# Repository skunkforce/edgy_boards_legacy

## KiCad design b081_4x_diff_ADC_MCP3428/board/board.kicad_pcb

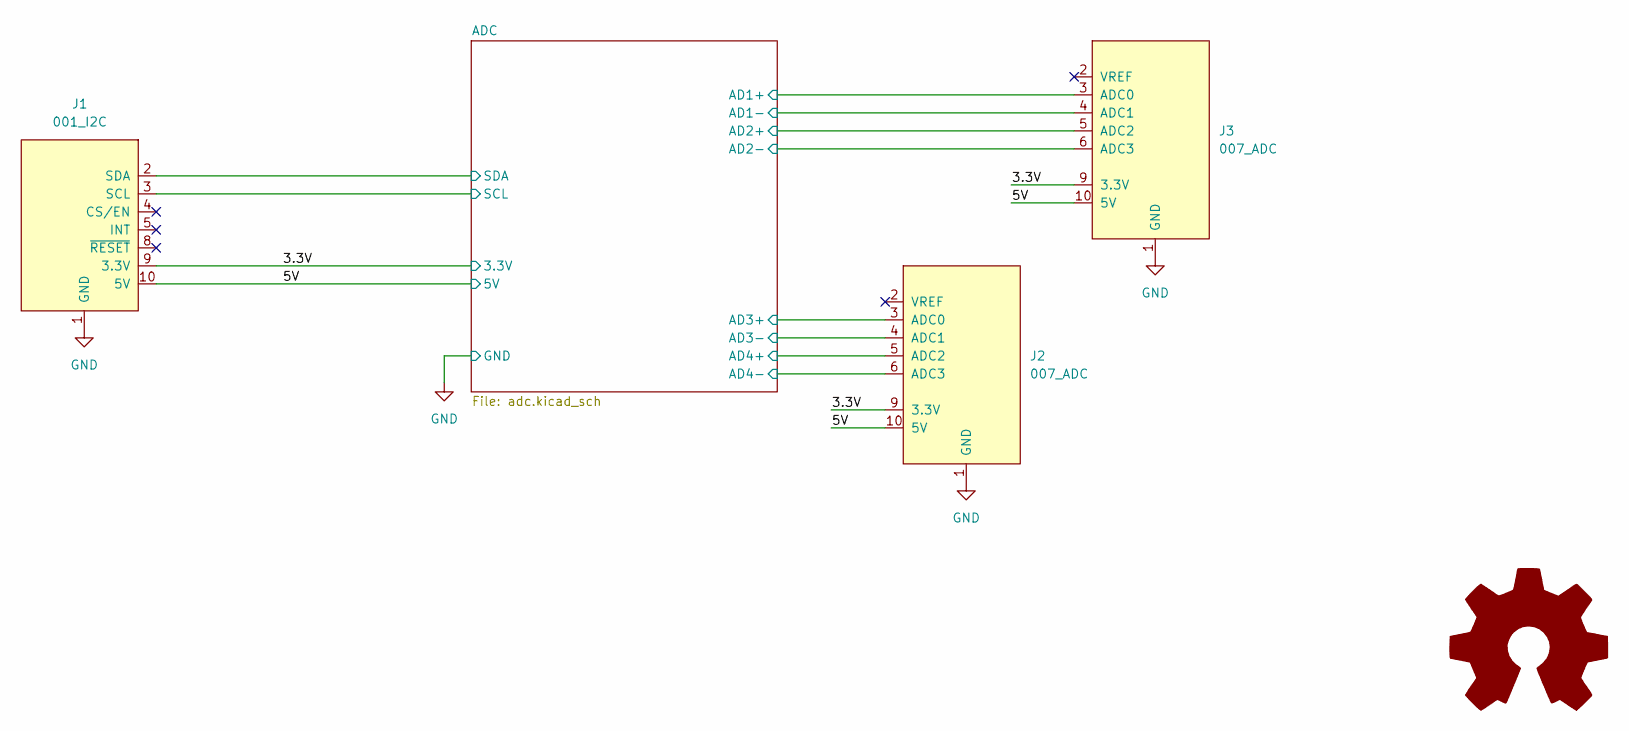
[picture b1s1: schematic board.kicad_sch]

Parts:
J1: 001_I2C; on_edge_2x05_device
J2, J3: 007_ADC; on_edge_2x05_host
l1: Logo_Open_Hardware_Larg; OSHW-Logo2_7.3x6mm_SilkScreen

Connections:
/3.3V: J1.9 (3.3V), J2.9 (3.3V), J3.9 (3.3V); also elsewhere on the board
/5V: J1.10 (5V), J2.10 (5V), J3.10 (5V); also elsewhere on the board
/ADC/AD1+: J3.3 (ADC0); also elsewhere on the board
/ADC/AD1-: J3.4 (ADC1); also elsewhere on the board
/ADC/AD2+: J3.5 (ADC2); also elsewhere on the board
/ADC/AD2-: J3.6 (ADC3); also elsewhere on the board
/ADC/AD3+: J2.3 (ADC0); also elsewhere on the board
/ADC/AD3-: J2.4 (ADC1); also elsewhere on the board
/ADC/AD4+: J2.5 (ADC2); also elsewhere on the board
/ADC/AD4-: J2.6 (ADC3); also elsewhere on the board
/ADC/SCL: J1.3 (SCL); also elsewhere on the board
/ADC/SDA: J1.2 (SDA); also elsewhere on the board
GND: J1.1 (GND), J2.1 (GND), J3.1 (GND); also elsewhere on the board

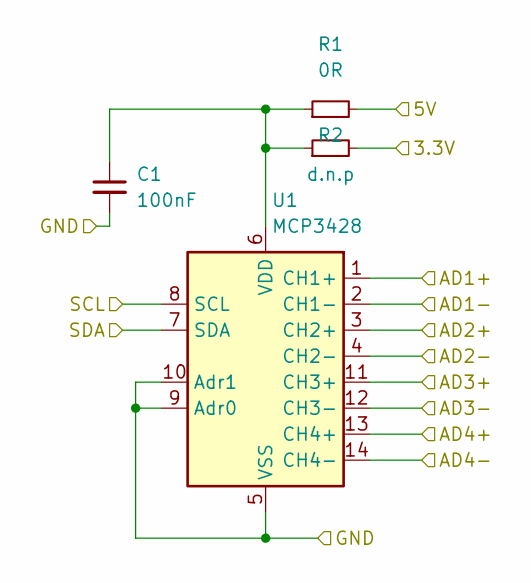
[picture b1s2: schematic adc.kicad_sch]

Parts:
C1: 100nF; C_0603_1608Metric
R1: 0R; R_0603_1608Metric
R2: d.n.p; R_0603_1608Metric
U1: MCP3428; SOIC-14_3.9x8.7mm_P1.27mm

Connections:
/3.3V: R2.2; also elsewhere on the board
/5V: R1.2; also elsewhere on the board
/ADC/AD1+: U1.1 (CH1+); also elsewhere on the board
/ADC/AD1-: U1.2 (CH1-); also elsewhere on the board
/ADC/AD2+: U1.3 (CH2+); also elsewhere on the board
/ADC/AD2-: U1.4 (CH2-); also elsewhere on the board
/ADC/AD3+: U1.11 (CH3+); also elsewhere on the board
/ADC/AD3-: U1.12 (CH3-); also elsewhere on the board
/ADC/AD4+: U1.13 (CH4+); also elsewhere on the board
/ADC/AD4-: U1.14 (CH4-); also elsewhere on the board
/ADC/SCL: U1.8 (SCL); also elsewhere on the board
/ADC/SDA: U1.7 (SDA); also elsewhere on the board
GND: C1.2, U1.5 (VSS), U1.9 (Adr0), U1.10 (Adr1); also elsewhere on the board
unnamed: C1.1, R1.1, R2.1, U1.6 (VDD)

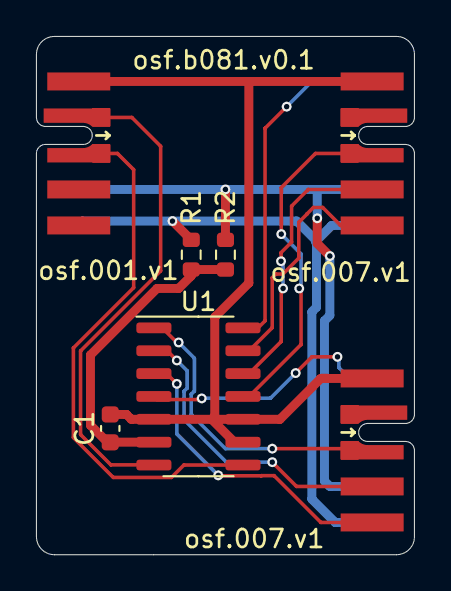
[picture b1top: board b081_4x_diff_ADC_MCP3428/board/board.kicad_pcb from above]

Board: 4 copper layers, 21.0 x 28.8 mm, 8 parts (1 on the bottom side), 14 nets.

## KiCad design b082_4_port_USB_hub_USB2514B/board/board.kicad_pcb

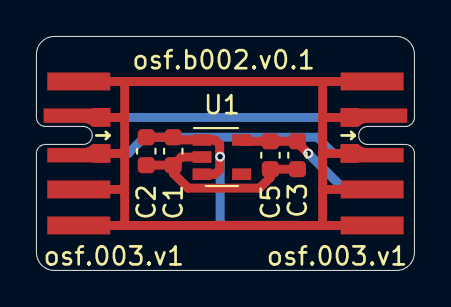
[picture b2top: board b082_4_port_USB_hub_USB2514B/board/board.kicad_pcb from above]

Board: 4 copper layers, 21.0 x 13.0 mm, 8 parts (1 on the bottom side), 7 nets.

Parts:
C1: 100nF; C_0603_1608Metric
C2, C5: 1uF; C_0603_1608Metric
C3: 10uF; C_0603_1608Metric
J1: 003_power; on_edge_2x05_device
J2: 003_power; on_edge_2x05_host
U1: TC1017-xCT; SOT-23-5
l1: Logo_Open_Hardware_Larg; OSHW-Logo2_7.3x6mm_SilkScreen

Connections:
GND: C1.2, C2.2, C3.2, C5.2, U1.2 (GND)
unnamed: C1.1, C2.1, J1.10 (5V), J2.10 (5V), U1.1 (VIN), U1.3 (~SHDN)
unnamed: C3.1, C5.1, J2.9 (3.3V), U1.5 (VOUT)
unnamed: J1.1 (GND), J1.2 (GND), J1.3 (GND), J1.4 (GND), J1.5 (GND), J2.1 (GND), J2.2 (GND), J2.3 (GND), J2.4 (GND), J2.5 (GND)
unnamed: J1.6 (1.2V), J2.6 (1.2V)
unnamed: J1.7 (1.8V), J2.7 (1.8V)
unnamed: J1.8 (2.5V), J2.8 (2.5V)

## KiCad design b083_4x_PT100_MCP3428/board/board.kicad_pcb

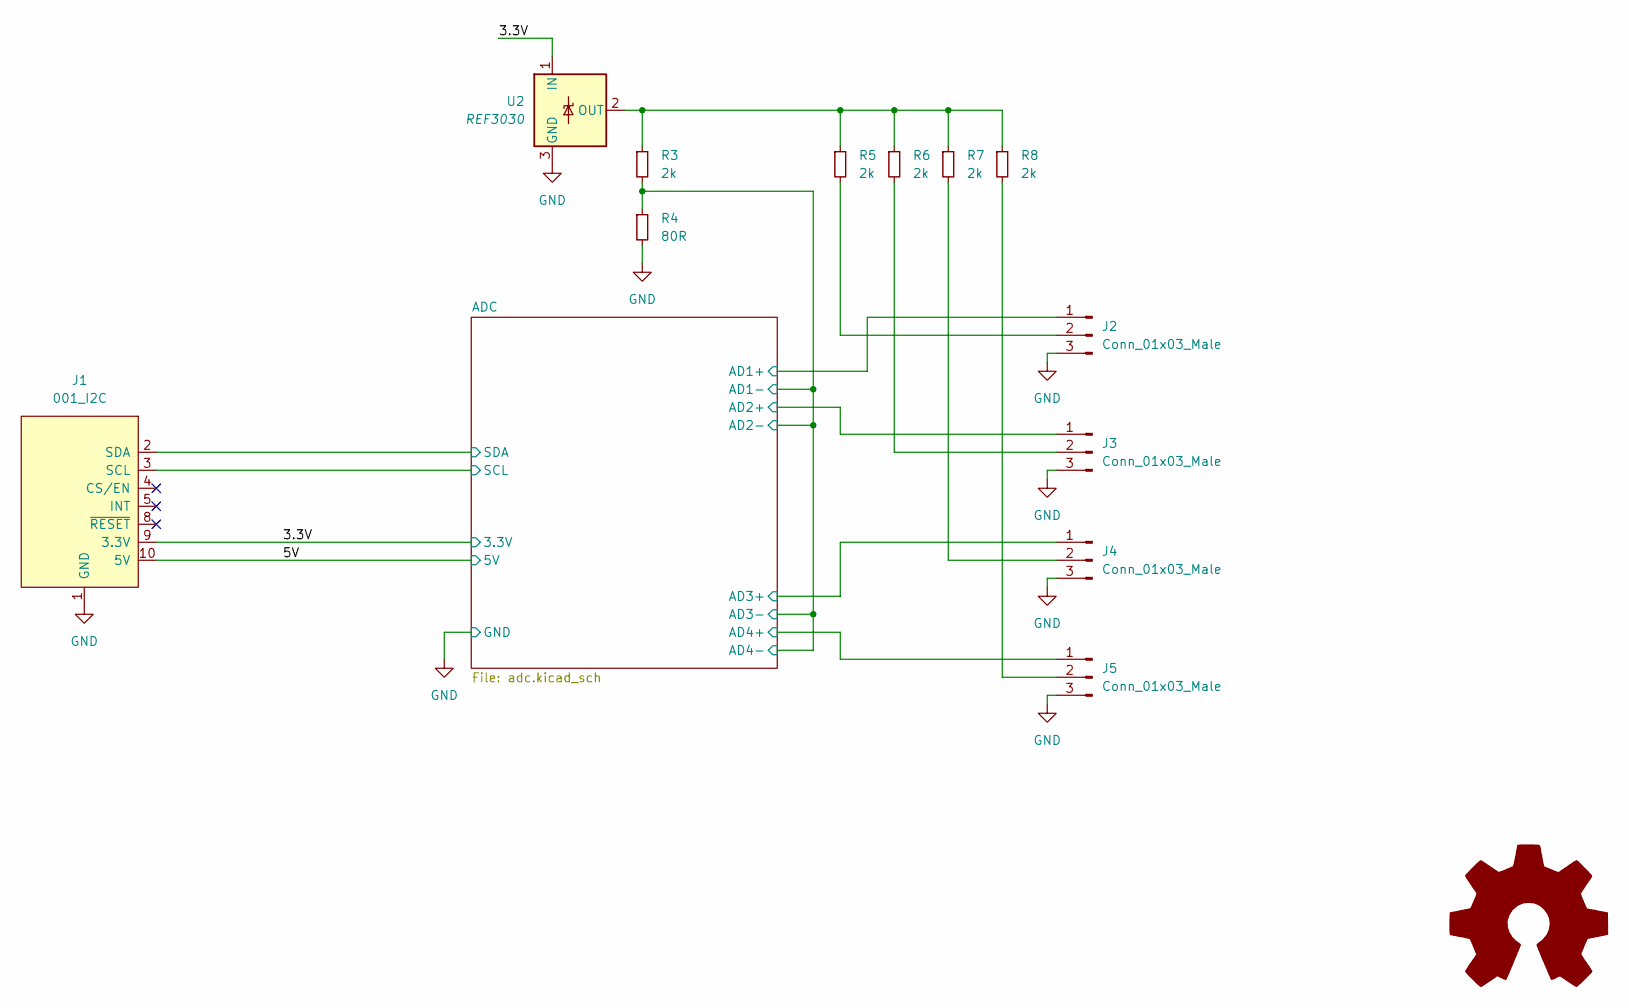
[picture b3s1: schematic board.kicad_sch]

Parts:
J1: 001_I2C; on_edge_2x05_device
J2, J3, J4, J5: Conn_01x03_Male; PinHeader_1x03_P2.54mm_Vertical
R3, R5, R6, R7, R8: 2k; R_0603_1608Metric
R4: 80R; R_0603_1608Metric
U2: REF3030; SOT-23
l1: Logo_Open_Hardware_Larg; OSHW-Logo2_7.3x6mm_SilkScreen

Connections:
/3.3V: J1.9 (3.3V), U2.1 (IN); also elsewhere on the board
/5V: J1.10 (5V)
/ADC/AD1+: J2.1; also elsewhere on the board
/ADC/AD1-: R3.2, R4.1; also elsewhere on the board
/ADC/AD2+: J3.1; also elsewhere on the board
/ADC/AD3+: J4.1; also elsewhere on the board
/ADC/AD4+: J5.1; also elsewhere on the board
/ADC/SCL: J1.3 (SCL); also elsewhere on the board
/ADC/SDA: J1.2 (SDA); also elsewhere on the board
GND: J1.1 (GND), J2.3, J3.3, J4.3, J5.3, R4.2, U2.3 (GND); also elsewhere on the board
unnamed: J2.2, R5.2
unnamed: J3.2, R6.2
unnamed: J4.2, R7.2
unnamed: J5.2, R8.2
unnamed: R3.1, R5.1, R6.1, R7.1, R8.1, U2.2 (OUT)

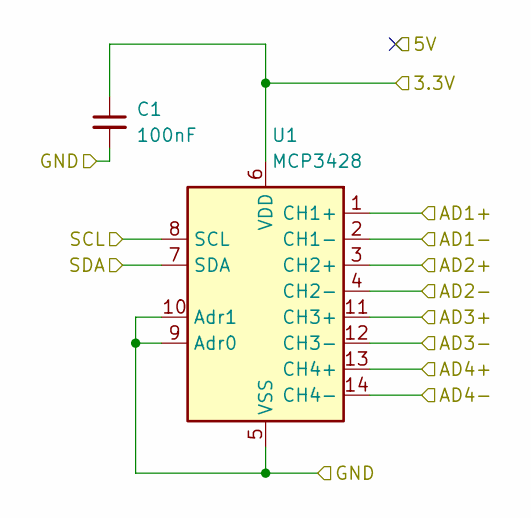
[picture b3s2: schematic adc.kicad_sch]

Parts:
C1: 100nF; C_0603_1608Metric
U1: MCP3428; SOIC-14_3.9x8.7mm_P1.27mm

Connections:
/3.3V: C1.1, U1.6 (VDD); also elsewhere on the board
/ADC/AD1+: U1.1 (CH1+); also elsewhere on the board
/ADC/AD1-: U1.2 (CH1-), U1.4 (CH2-), U1.12 (CH3-), U1.14 (CH4-); also elsewhere on the board
/ADC/AD2+: U1.3 (CH2+); also elsewhere on the board
/ADC/AD3+: U1.11 (CH3+); also elsewhere on the board
/ADC/AD4+: U1.13 (CH4+); also elsewhere on the board
/ADC/SCL: U1.8 (SCL); also elsewhere on the board
/ADC/SDA: U1.7 (SDA); also elsewhere on the board
GND: C1.2, U1.5 (VSS), U1.9 (Adr0), U1.10 (Adr1); also elsewhere on the board

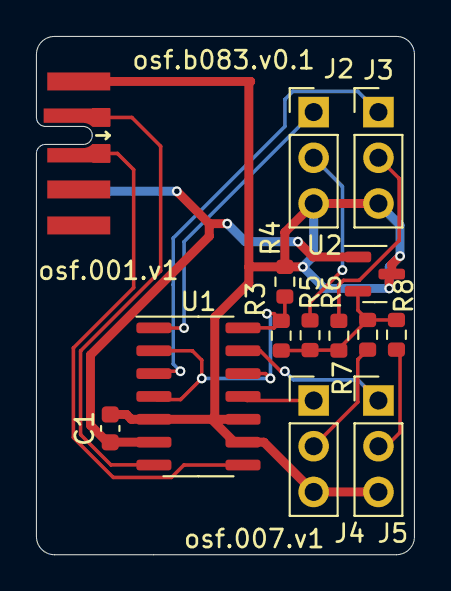
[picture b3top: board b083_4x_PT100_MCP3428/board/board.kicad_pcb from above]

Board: 4 copper layers, 21.0 x 28.8 mm, 15 parts (1 on the bottom side), 14 nets.

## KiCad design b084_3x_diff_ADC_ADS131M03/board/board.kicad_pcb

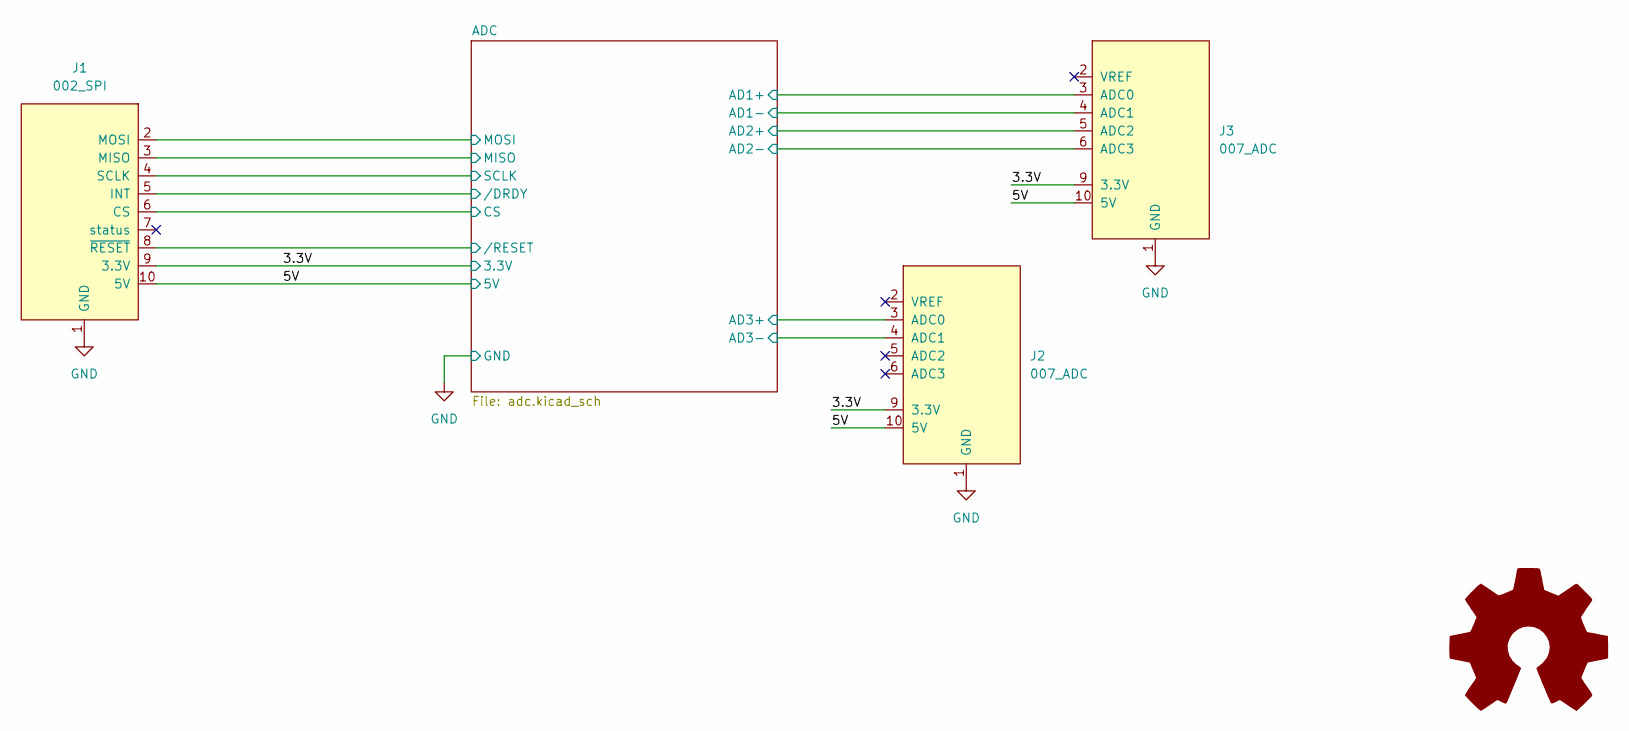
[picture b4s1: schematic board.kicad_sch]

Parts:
J1: 002_SPI; on_edge_2x05_device
J2, J3: 007_ADC; on_edge_2x05_host
l1: Logo_Open_Hardware_Larg; OSHW-Logo2_7.3x6mm_SilkScreen

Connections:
/3.3V: J1.9 (3.3V), J2.9 (3.3V), J3.9 (3.3V); also elsewhere on the board
/5V: J1.10 (5V), J2.10 (5V), J3.10 (5V)
/ADC/AD1+: J3.3 (ADC0); also elsewhere on the board
/ADC/AD1-: J3.4 (ADC1); also elsewhere on the board
/ADC/AD2+: J3.5 (ADC2); also elsewhere on the board
/ADC/AD2-: J3.6 (ADC3); also elsewhere on the board
/ADC/AD3+: J2.3 (ADC0); also elsewhere on the board
/ADC/AD3-: J2.4 (ADC1); also elsewhere on the board
/ADC/CS: J1.6 (CS); also elsewhere on the board
/ADC/MISO: J1.3 (MISO); also elsewhere on the board
/ADC/MOSI: J1.2 (MOSI); also elsewhere on the board
/ADC/SCLK: J1.4 (SCLK); also elsewhere on the board
/ADC//DRDY: J1.5 (INT); also elsewhere on the board
/ADC//RESET: J1.8 (~RESET); also elsewhere on the board
GND: J1.1 (GND), J2.1 (GND), J3.1 (GND); also elsewhere on the board

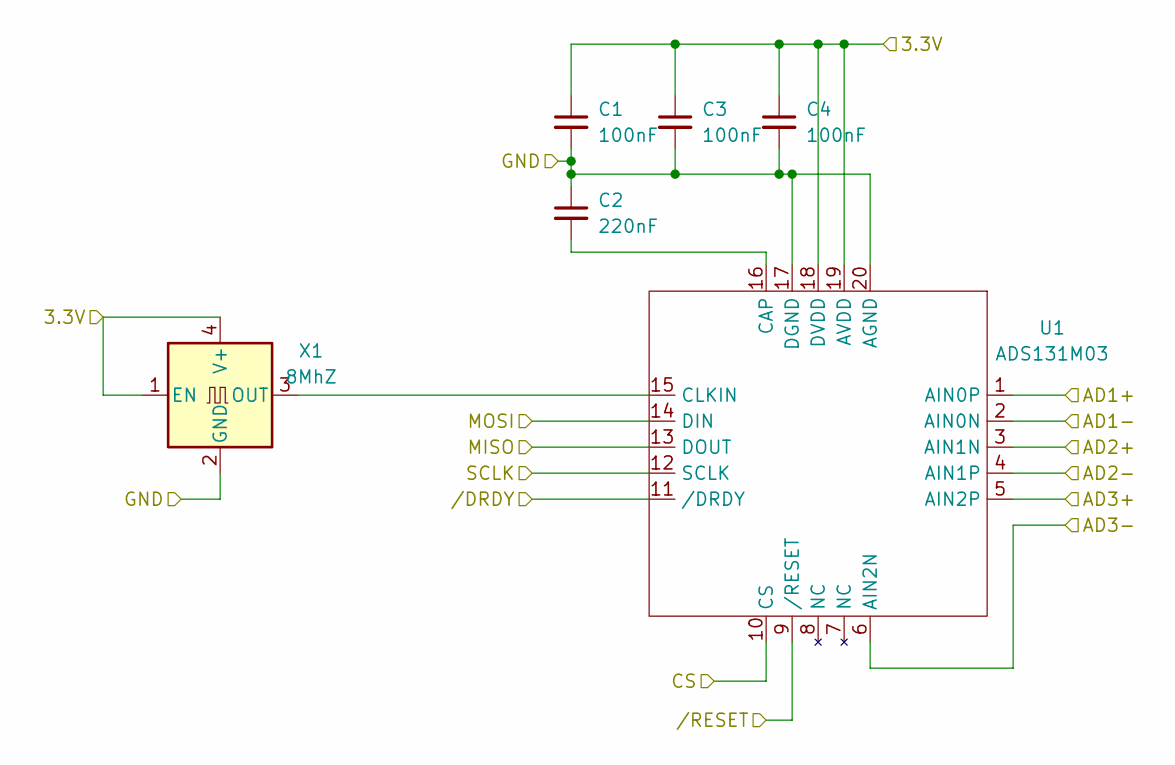
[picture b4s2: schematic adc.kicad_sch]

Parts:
C1, C3, C4: 100nF; C_0603_1608Metric
C2: 220nF; C_0603_1608Metric
U1: ADS131M03; WQFN-20-1EP_3x3mm_P0.4mm_EP1.7x1.7mm
X1: 8MhZ; Oscillator_SMD_EuroQuartz_XO32-4Pin_3.2x2.5mm; MPN O 8,0-JO32-B-1V3-1-T1-LF

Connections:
/3.3V: C1.1, C3.1, C4.1, U1.18 (DVDD), U1.19 (AVDD), X1.1 (EN), X1.4 (V+); also elsewhere on the board
/ADC/AD1+: U1.1 (AIN0P); also elsewhere on the board
/ADC/AD1-: U1.2 (AIN0N); also elsewhere on the board
/ADC/AD2+: U1.3 (AIN1N); also elsewhere on the board
/ADC/AD2-: U1.4 (AIN1P); also elsewhere on the board
/ADC/AD3+: U1.5 (AIN2P); also elsewhere on the board
/ADC/AD3-: U1.6 (AIN2N); also elsewhere on the board
/ADC/CS: U1.10 (CS); also elsewhere on the board
/ADC/MISO: U1.13 (DOUT); also elsewhere on the board
/ADC/MOSI: U1.14 (DIN); also elsewhere on the board
/ADC/SCLK: U1.12 (SCLK); also elsewhere on the board
/ADC//DRDY: U1.11 (/DRDY); also elsewhere on the board
/ADC//RESET: U1.9 (/RESET); also elsewhere on the board
GND: C1.2, C2.1, C3.2, C4.2, U1.17 (DGND), U1.20 (AGND), X1.2 (GND); also elsewhere on the board
unnamed: C2.2, U1.16 (CAP)
unnamed: U1.15 (CLKIN), X1.3 (OUT)

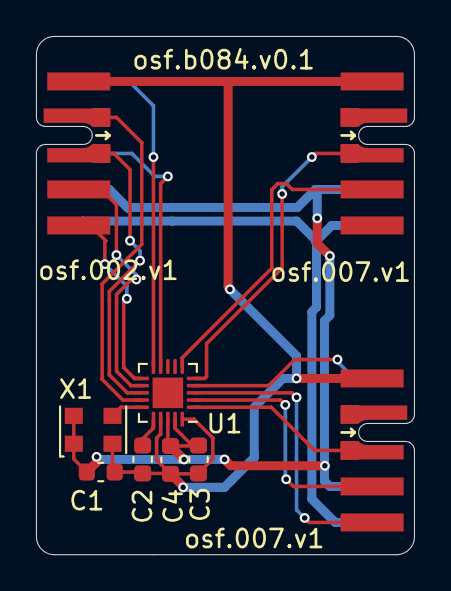
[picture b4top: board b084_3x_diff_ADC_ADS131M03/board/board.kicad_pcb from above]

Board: 4 copper layers, 21.0 x 28.8 mm, 10 parts (1 on the bottom side), 17 nets.

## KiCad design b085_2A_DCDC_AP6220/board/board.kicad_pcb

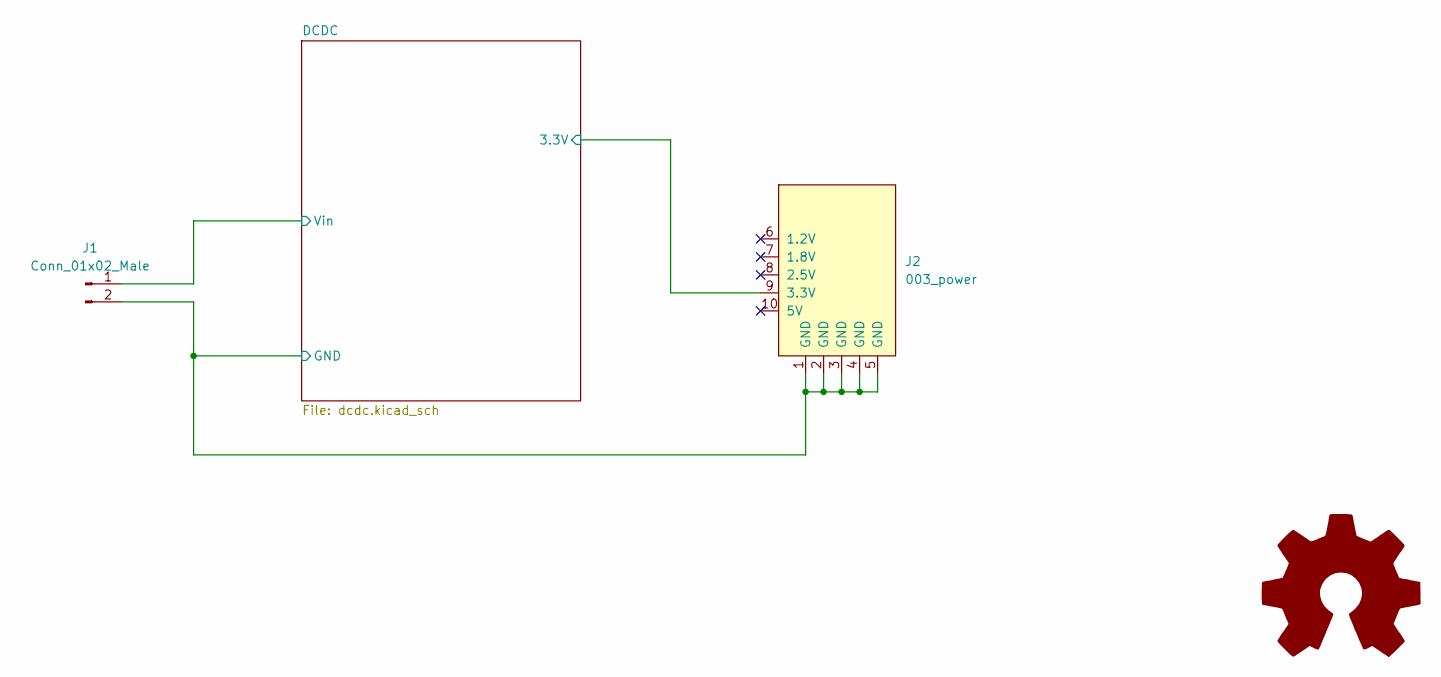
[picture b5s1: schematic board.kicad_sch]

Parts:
J1: Conn_01x02_Male; PinHeader_1x02_P2.54mm_Vertical
J2: 003_power; on_edge_2x05_host
l1: Logo_Open_Hardware_Larg; OSHW-Logo2_7.3x6mm_SilkScreen

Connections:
/DCDC/3.3V: J2.9 (3.3V); also elsewhere on the board
/DCDC/GND: J1.2, J2.1 (GND), J2.2 (GND), J2.3 (GND), J2.4 (GND), J2.5 (GND); also elsewhere on the board
/DCDC/Vin: J1.1; also elsewhere on the board

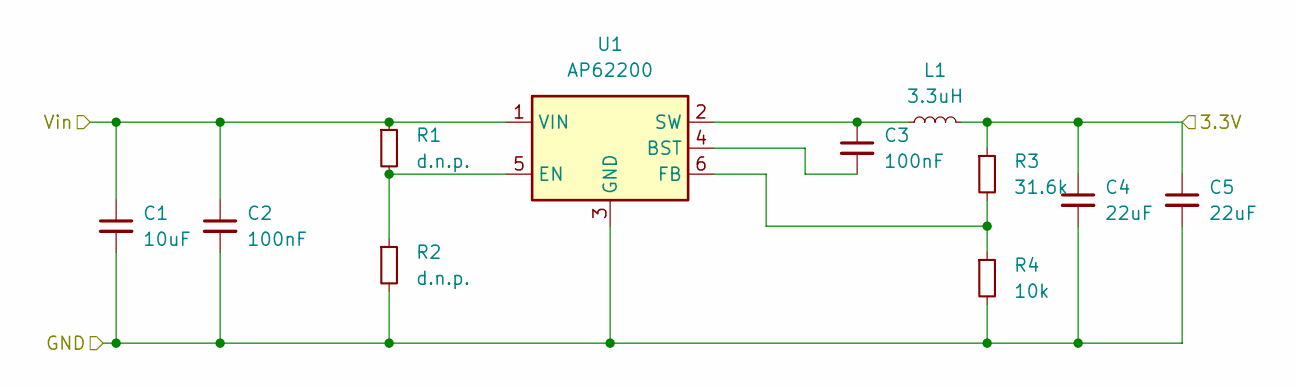
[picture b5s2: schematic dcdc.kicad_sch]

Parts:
C1: 10uF; C_0805_2012Metric; Voltage 16V
C2, C3: 100nF; C_0603_1608Metric
C4, C5: 22uF; C_0805_2012Metric; Voltage 6.3V
L1: 3.3uH; L_Bourns-SRN4018; MPN NRS5024T330MMGJ
R1, R2: d.n.p.; R_0603_1608Metric
R3: 31.6k; R_0603_1608Metric
R4: 10k; R_0603_1608Metric
U1: AP62200; SOT-563; MPN AP62200Z6-7

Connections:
/DCDC/3.3V: C4.1, C5.1, L1.2, R3.1; also elsewhere on the board
/DCDC/GND: C1.2, C2.2, C4.2, C5.2, R2.2, R4.2, U1.3 (GND); also elsewhere on the board
/DCDC/Vin: C1.1, C2.1, R1.1, U1.1 (VIN); also elsewhere on the board
unnamed: C3.1, L1.1, U1.2 (SW)
unnamed: C3.2, U1.4 (BST)
unnamed: R1.2, R2.1, U1.5 (EN)
unnamed: R3.2, R4.1, U1.6 (FB)

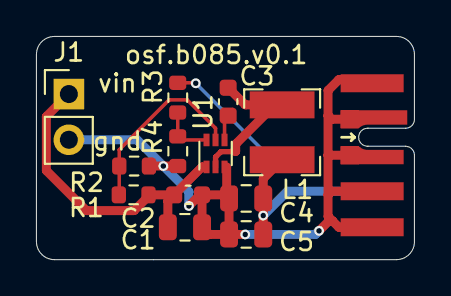
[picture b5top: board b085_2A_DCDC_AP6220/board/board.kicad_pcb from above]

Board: 4 copper layers, 21.0 x 12.4 mm, 14 parts (1 on the bottom side), 7 nets.

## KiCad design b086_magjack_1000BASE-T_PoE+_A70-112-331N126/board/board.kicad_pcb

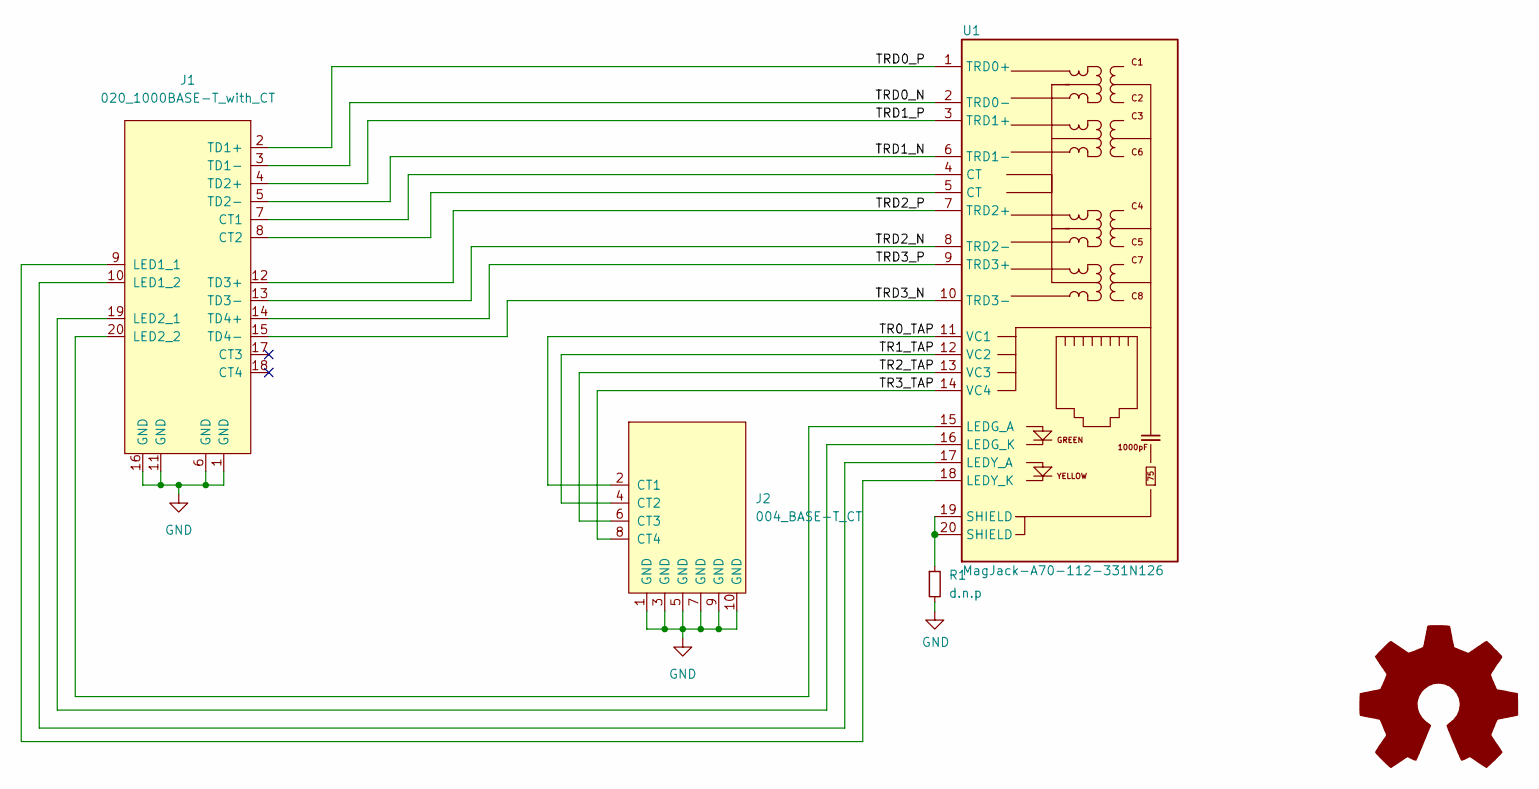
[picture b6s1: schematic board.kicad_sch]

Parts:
J1: 020_1000BASE-T_with_CT; on_edge_2x10_device
J2: 004_BASE-T_CT; on_edge_2x05_host
R1: d.n.p; R_1206_3216Metric
U1: MagJack-A70-112-331N126; TRJG0926HENL; Part Description Gigabit Ethernet Magjack
l1: Logo_Open_Hardware_Larg; OSHW-Logo2_7.3x6mm_SilkScreen

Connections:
/TR0_TAP: J2.2 (CT1), U1.11 (VC1)
/TR1_TAP: J2.4 (CT2), U1.12 (VC2)
/TR2_TAP: J2.6 (CT3), U1.13 (VC3)
/TR3_TAP: J2.8 (CT4), U1.14 (VC4)
/TRD0_N: J1.3 (TD1-), U1.2 (TRD0-)
/TRD0_P: J1.2 (TD1+), U1.1 (TRD0+)
/TRD1_N: J1.5 (TD2-), U1.6 (TRD1-)
/TRD1_P: J1.4 (TD2+), U1.3 (TRD1+)
/TRD2_N: J1.13 (TD3-), U1.8 (TRD2-)
/TRD2_P: J1.12 (TD3+), U1.7 (TRD2+)
/TRD3_N: J1.15 (TD4-), U1.10 (TRD3-)
/TRD3_P: J1.14 (TD4+), U1.9 (TRD3+)
GND: J1.1 (GND), J1.6 (GND), J1.11 (GND), J1.16 (GND), J2.1 (GND), J2.3 (GND), J2.5 (GND), J2.7 (GND), J2.9 (GND), J2.10 (GND), R1.2
unnamed: J1.7 (CT1), U1.4 (CT)
unnamed: J1.8 (CT2), U1.5 (CT)
unnamed: J1.9 (LED1_1), U1.18 (LEDY_K)
unnamed: J1.10 (LED1_2), U1.17 (LEDY_A)
unnamed: J1.19 (LED2_1), U1.16 (LEDG_K)
unnamed: J1.20 (LED2_2), U1.15 (LEDG_A)
unnamed: R1.1, U1.19 (SHIELD), U1.20 (SHIELD)

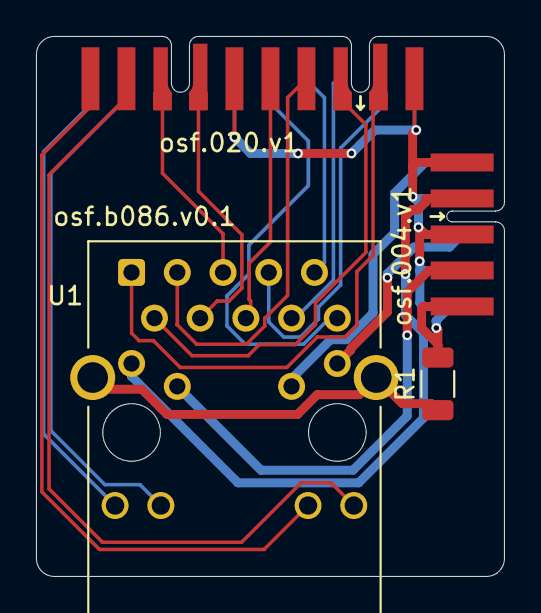
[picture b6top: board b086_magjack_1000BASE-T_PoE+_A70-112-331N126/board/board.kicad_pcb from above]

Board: 2 copper layers, 26.0 x 30.0 mm, 5 parts (1 on the bottom side), 20 nets.

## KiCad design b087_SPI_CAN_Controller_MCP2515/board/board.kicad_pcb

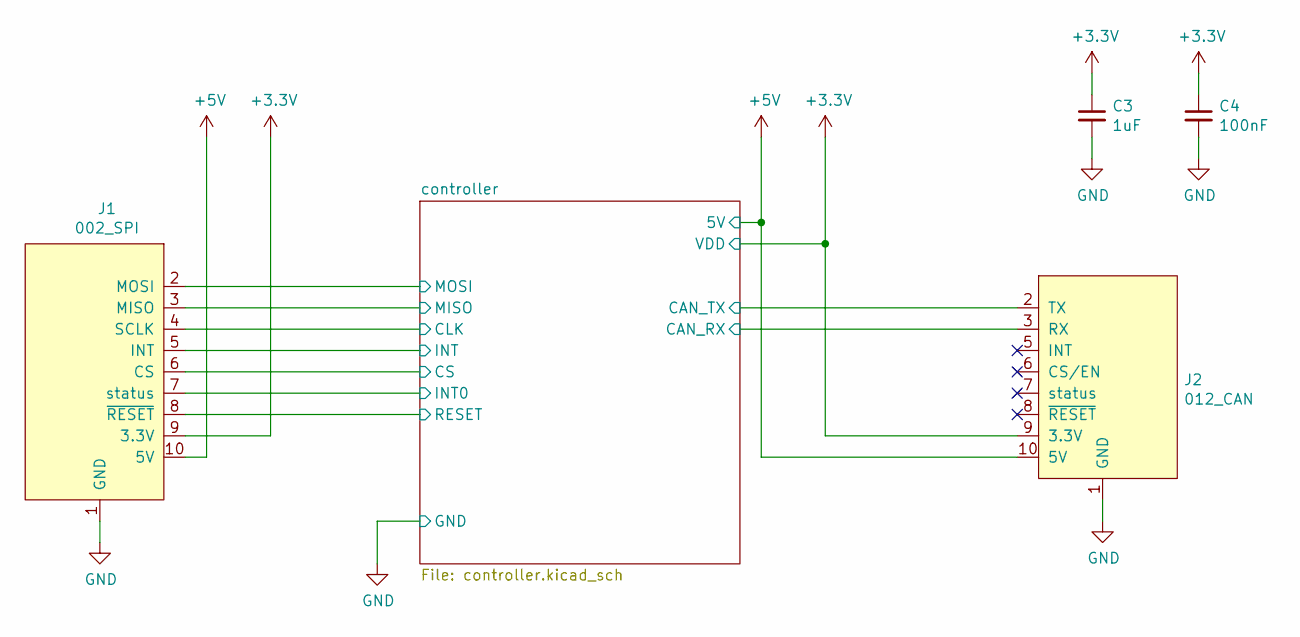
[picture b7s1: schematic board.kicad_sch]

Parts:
C3: 1uF; C_0603_1608Metric; Voltage 6.3V
C4: 100nF; C_0603_1608Metric; Voltage 6.3V
J1: 002_SPI; on_edge_2x05_device
J2: 012_CAN; on_edge_2x05_host

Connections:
+3V3: C3.1, C4.1, J1.9 (3.3V), J2.9 (3.3V); also elsewhere on the board
+5V: J1.10 (5V), J2.10 (5V)
/controller/CAN_RX: J2.3 (RX); also elsewhere on the board
/controller/CAN_TX: J2.2 (TX); also elsewhere on the board
/controller/CLK: J1.4 (SCLK); also elsewhere on the board
/controller/CS: J1.6 (CS); also elsewhere on the board
/controller/INT: J1.5 (INT); also elsewhere on the board
/controller/INT0: J1.7 (status); also elsewhere on the board
/controller/MISO: J1.3 (MISO); also elsewhere on the board
/controller/MOSI: J1.2 (MOSI); also elsewhere on the board
/controller/RESET: J1.8 (~RESET); also elsewhere on the board
GND: C3.2, C4.2, J1.1 (GND), J2.1 (GND); also elsewhere on the board

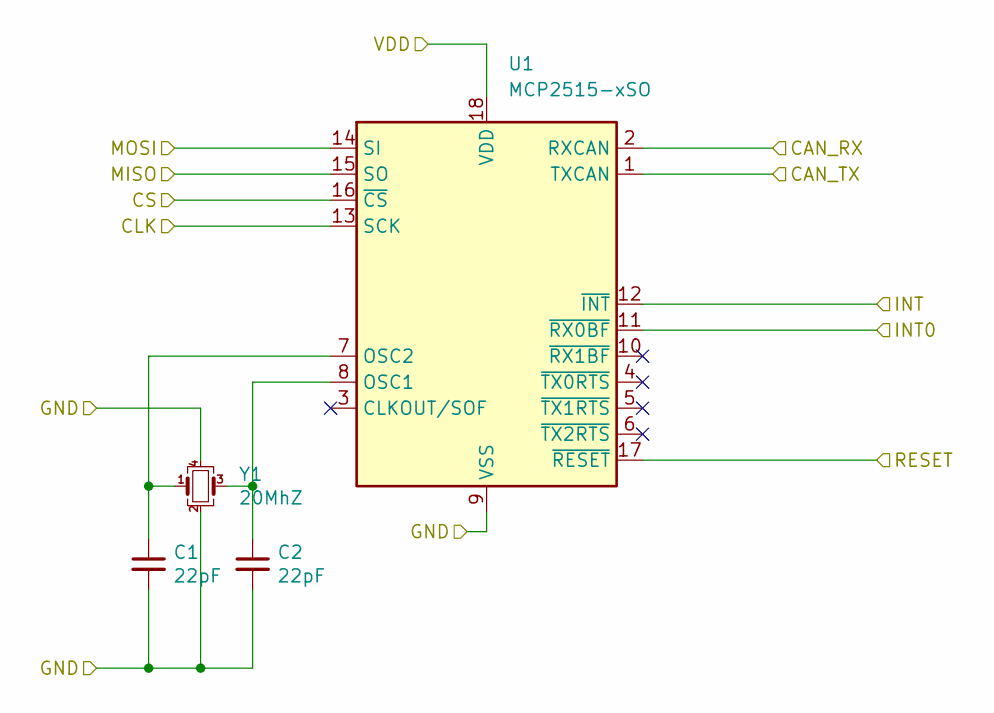
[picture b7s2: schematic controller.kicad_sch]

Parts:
C1, C2: 22pF; C_0603_1608Metric; Voltage 6.3V
U1: MCP2515-xSO; SOIC-18W_7.5x11.6mm_P1.27mm
Y1: 20MhZ; Crystal_SMD_Abracon_ABM8G-4Pin_3.2x2.5mm; MPN ECS-200-18-33-JGN-TR

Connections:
+3V3: U1.18 (VDD); also elsewhere on the board
/controller/CAN_RX: U1.2 (RXCAN); also elsewhere on the board
/controller/CAN_TX: U1.1 (TXCAN); also elsewhere on the board
/controller/CLK: U1.13 (SCK); also elsewhere on the board
/controller/CS: U1.16 (~CS); also elsewhere on the board
/controller/INT: U1.12 (~INT); also elsewhere on the board
/controller/INT0: U1.11 (~RX0BF); also elsewhere on the board
/controller/MISO: U1.15 (SO); also elsewhere on the board
/controller/MOSI: U1.14 (SI); also elsewhere on the board
/controller/RESET: U1.17 (~RESET); also elsewhere on the board
GND: C1.2, C2.2, U1.9 (VSS), Y1.2, Y1.4; also elsewhere on the board
unnamed: C1.1, U1.7 (OSC2), Y1.1
unnamed: C2.1, U1.8 (OSC1), Y1.3

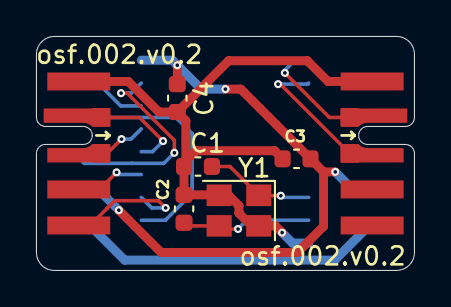
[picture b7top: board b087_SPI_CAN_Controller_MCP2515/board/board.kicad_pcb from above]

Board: 2 copper layers, 21.0 x 13.0 mm, 8 parts (1 on the bottom side), 14 nets.

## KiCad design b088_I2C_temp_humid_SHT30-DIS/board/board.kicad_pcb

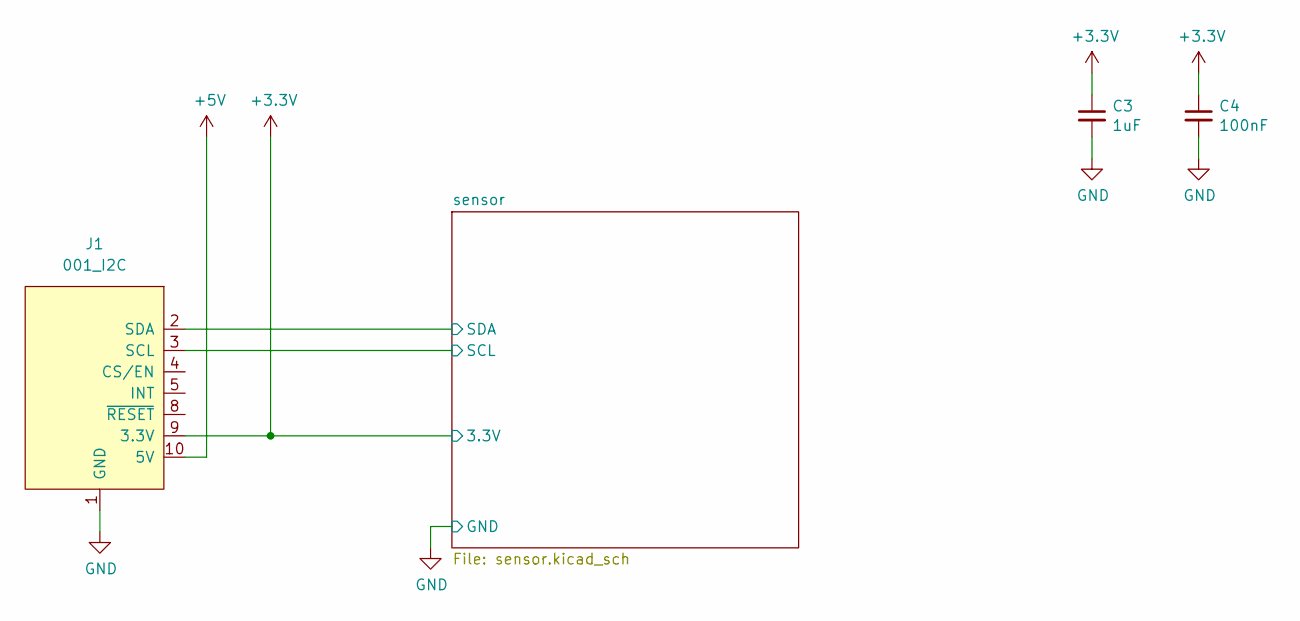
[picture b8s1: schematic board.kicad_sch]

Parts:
C3: 1uF; C_0603_1608Metric; Voltage 6.3V
C4: 100nF; C_0603_1608Metric; Voltage 6.3V
J1: 001_I2C; on_edge_2x05_device

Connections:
+3V3: C3.1, C4.1, J1.9 (3.3V); also elsewhere on the board
+5V: J1.10 (5V)
/sensor/SCL: J1.3 (SCL); also elsewhere on the board
/sensor/SDA: J1.2 (SDA); also elsewhere on the board
GND: C3.2, C4.2, J1.1 (GND); also elsewhere on the board

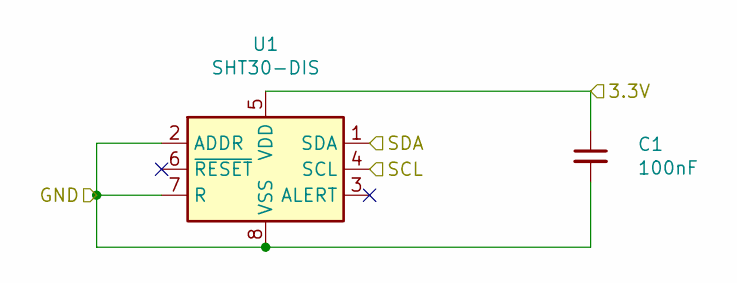
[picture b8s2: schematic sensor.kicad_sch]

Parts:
C1: 100nF; C_0603_1608Metric
U1: SHT30-DIS; Sensirion_DFN-8-1EP_2.5x2.5mm_P0.5mm_EP1.1x1.7mm

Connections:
+3V3: C1.1, U1.5 (VDD); also elsewhere on the board
/sensor/SCL: U1.4 (SCL); also elsewhere on the board
/sensor/SDA: U1.1 (SDA); also elsewhere on the board
GND: C1.2, U1.2 (ADDR), U1.7 (R), U1.8 (VSS), U1.9 (VSS); also elsewhere on the board
